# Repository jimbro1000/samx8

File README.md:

---
title: 'SAMx8: Dragon 64 512K SRAM board'
author:
- Ciaran Anscomb
...

Iterating on the SAMx4, the SAMx8 is a 512K RAM expansion and MMU for the
Dragon 64.  It enables arbitrary mapping of 16K pages in two tasks, optionally
making either of the highest two 4K areas common to all memory maps.

Because fast SRAM is used, and because the SAMx8 completely replaces the SAM,
video can be supported when the CPU is running at double rate.  The video base
address can be set to any multiple of 32 bytes across the entire 512K.

As this was partly an exercise in seeing what could be fit into the same sized
CPLD as the SAMx4, some features of the SAM are lost, e.g. Address-Dependent
CPU rate and the undocumented video address "glitching".

This design selects components available at the time of writing, but it should
be noted that some of these are end of life.  Hopefully, the VHDL code being
available will enable similar small and cheap designs with alternate
programmable logic chips.

**Warning:** Fitting this board requires a modification to the original
motherboard.  Although the Dragon 64 PCB is pretty robust, this is old
hardware, so I do not recommend trying this if you're not confident in your
desoldering skills: lifted pads or tracks may ensue.

Released under the Creative Commons Attribution-ShareAlike 4.0 International
License (CC BY-SA 4.0).  Full text in the LICENSE file.

## Files

`pcb/` contains KiCad schematic and PCB designs.

`cpld/` contains VHDL source for the Xilinx XC95144XL CPLD.  Either open the
`samx8.xise` project file in ISE or source the ISE environment files and run
`make` in this directory (GNU Make required).

`doc/` contains LaTeX and drawtiming source for the documentation.

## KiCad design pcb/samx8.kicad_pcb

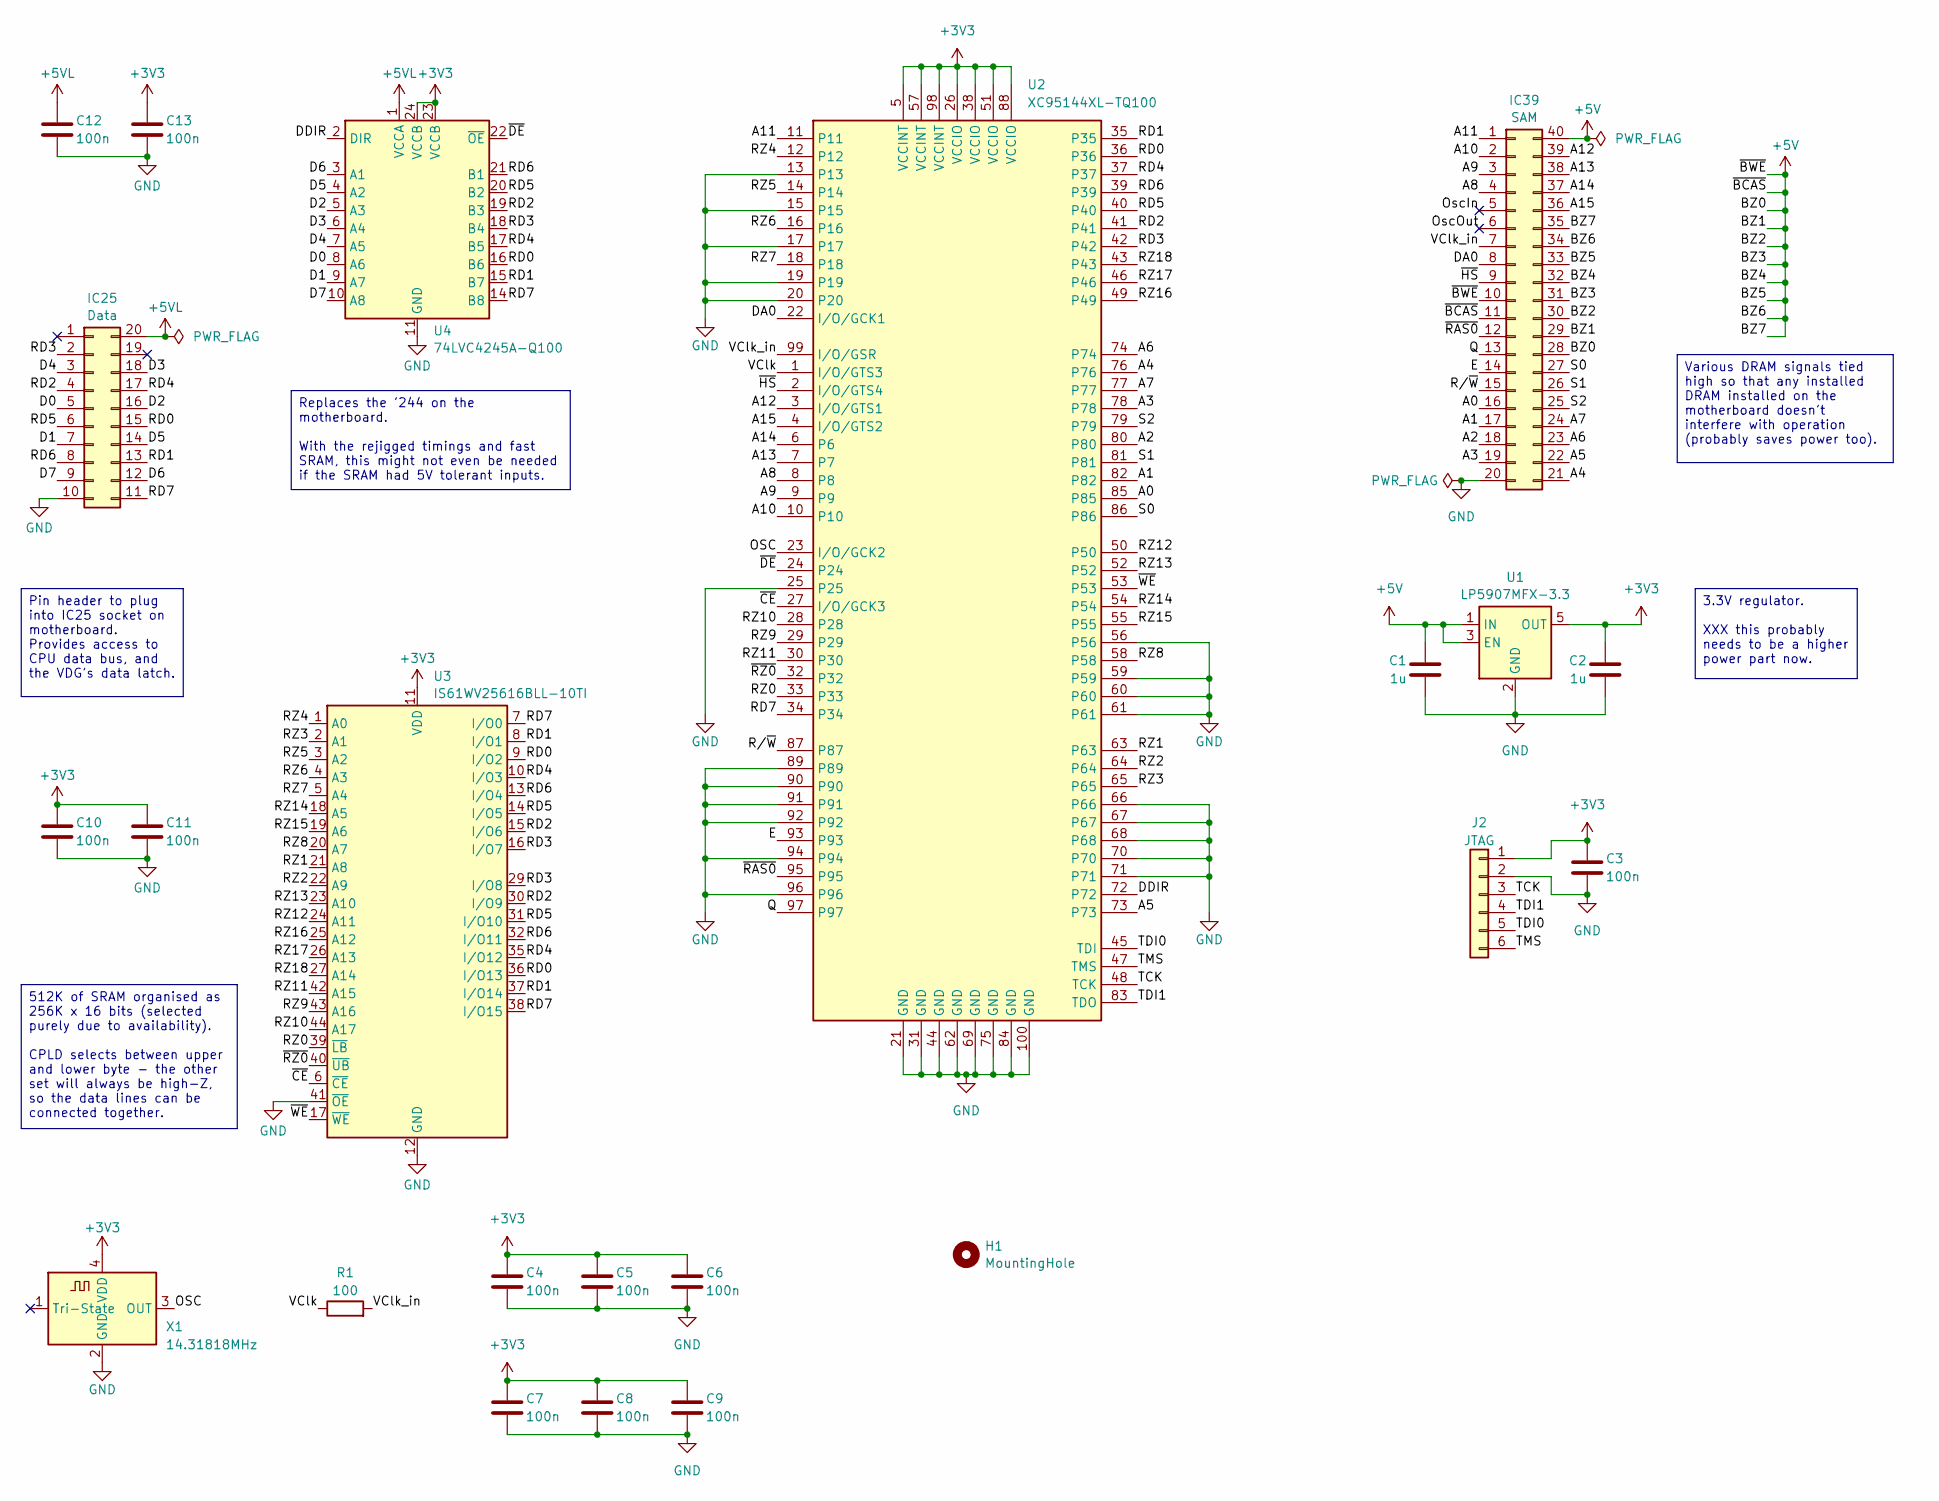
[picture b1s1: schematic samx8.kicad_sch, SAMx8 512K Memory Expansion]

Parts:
C1, C2: 1u; C_0805_2012Metric; LCSC Part C28323
C3, C4, C5, C6, C7, C8, C9, C10, C11, C12, C13: 100n; C_0402_1005Metric; JLCPCB BOM 0
H1: MountingHole; MountingHole_2.2mm_M2
IC25: Data; DIP-20_W7.62mm
IC39: SAM; DIP-40_W15.24mm; JLCPCB BOM 0
J2: JTAG; PinHeader_1x06_P2.54mm_Vertical; JLCPCB BOM 0
R1: 100; R_0603_1608Metric; LCSC Part C22775
U1: LP5907MFX-3.3; SOT-23-5; LCSC Part C80670
U2: XC95144XL-TQ100; TQFP-100_14x14mm_P0.5mm; LCSC Part C45126
U3: IS61WV25616BLL-10TI; TSOP-II-44_10.16x18.41mm_P0.8mm; LCSC Part C53825
U4: 74LVC4245A-Q100; TSSOP-24_4.4x7.8mm_P0.65mm; LCSC Part C548801
X1: 14.31818MHz; Oscillator_SMD_ECS_2520MV-xxx-xx-4Pin_2.5x2.0mm; LCSC Part C5119017

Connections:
+3V3: C2.1, C3.1, C4.1, C5.1, C6.1, C7.1, C8.1, C9.1, C10.1, C11.1, C13.1, J2.1, U1.5 (OUT), U2.5 (VCCINT), U2.26 (VCCIO), U2.38 (VCCIO), U2.51 (VCCIO), U2.57 (VCCINT), U2.88 (VCCIO), U2.98 (VCCINT), U3.11 (VDD), U3.33 (VDD), U4.23 (VCCB), U4.24 (VCCB), X1.4 (VDD)
+5V: C1.1, IC39.10, IC39.11, IC39.28, IC39.29, IC39.30, IC39.31, IC39.32, IC39.33, IC39.34, IC39.35, IC39.40, U1.1 (IN), U1.3 (EN)
+5VL: C12.1, IC25.20, U4.1 (VCCA)
/A0: IC39.16, U2.85
/A1: IC39.17, U2.82
/A2: IC39.18, U2.80
/A3: IC39.19, U2.78
/A4: IC39.21, U2.76
/A5: IC39.22, U2.73
/A6: IC39.23, U2.74
/A7: IC39.24, U2.77
/A8: IC39.4, U2.8
/A9: IC39.3, U2.9
/A10: IC39.2, U2.10
/A11: IC39.1, U2.11
/A12: IC39.39, U2.3 (I/O/GTS1)
/A13: IC39.38, U2.7
/A14: IC39.37, U2.6
/A15: IC39.36, U2.4 (I/O/GTS2)
/D0: IC25.5, U4.8 (A6)
/D1: IC25.7, U4.9 (A7)
/D2: IC25.16, U4.5 (A3)
/D3: IC25.18, U4.6 (A4)
/D4: IC25.3, U4.7 (A5)
/D5: IC25.14, U4.4 (A2)
/D6: IC25.12, U4.3 (A1)
/D7: IC25.9, U4.10 (A8)
/DA0: IC39.8, U2.22 (I/O/GCK1)
/DDIR: U2.72, U4.2 (DIR)
/E: IC39.14, U2.93
/OSC: U2.23 (I/O/GCK2), X1.3 (OUT)
/OscIn: IC39.5
/OscOut: IC39.6
/Q: IC39.13, U2.97
/RD0: IC25.15, U2.36, U3.9 (I/O2), U3.36 (I/O13), U4.16 (B6)
/RD1: IC25.13, U2.35, U3.8 (I/O1), U3.37 (I/O14), U4.15 (B7)
/RD2: IC25.4, U2.41, U3.15 (I/O6), U3.30 (I/O9), U4.19 (B3)
/RD3: IC25.2, U2.42, U3.16 (I/O7), U3.29 (I/O8), U4.18 (B4)
/RD4: IC25.17, U2.37, U3.10 (I/O3), U3.35 (I/O12), U4.17 (B5)
/RD5: IC25.6, U2.40, U3.14 (I/O5), U3.31 (I/O10), U4.20 (B2)
/RD6: IC25.8, U2.39, U3.13 (I/O4), U3.32 (I/O11), U4.21 (B1)
/RD7: IC25.11, U2.34, U3.7 (I/O0), U3.38 (I/O15), U4.14 (B8)
/RZ0: U2.33, U3.39 (~LB)
/RZ1: U2.63, U3.21 (A8)
/RZ2: U2.64, U3.22 (A9)
/RZ3: U2.65, U3.2 (A1)
/RZ4: U2.12, U3.1 (A0)
/RZ5: U2.14, U3.3 (A2)
/RZ6: U2.16, U3.4 (A3)
/RZ7: U2.18, U3.5 (A4)
/RZ8: U2.58, U3.20 (A7)
/RZ9: U2.29, U3.43 (A16)
/RZ10: U2.28, U3.44 (A17)
/RZ11: U2.30, U3.42 (A15)
/RZ12: U2.50, U3.24 (A11)
/RZ13: U2.52, U3.23 (A10)
/RZ14: U2.54, U3.18 (A5)
/RZ15: U2.55, U3.19 (A6)
/RZ16: U2.49, U3.25 (A12)
/RZ17: U2.46, U3.26 (A13)
/RZ18: U2.43, U3.27 (A14)
/R/~W: IC39.15, U2.87
/S0: IC39.27, U2.86
/S1: IC39.26, U2.81
/S2: IC39.25, U2.79
/TCK: J2.3, U2.48 (TCK)
/TDI0: J2.5, U2.45 (TDI)
/TDI1: J2.4, U2.83 (TDO)
/TMS: J2.6, U2.47 (TMS)
/VClk: R1.1, U2.1 (I/O/GTS3)
/VClk_in: IC39.7, R1.2, U2.99 (I/O/GSR)
/~CE: U2.27 (I/O/GCK3), U3.6 (~CE)
/~DE: U2.24, U4.22 (~OE)
/~HS: IC39.9, U2.2 (I/O/GTS4)
/~RAS0: IC39.12, U2.95
/~RZ0: U2.32, U3.40 (~UB)
/~WE: U2.53, U3.17 (~WE)
GND: C1.2, C2.2, C3.2, C4.2, C5.2, C6.2, C7.2, C8.2, C9.2, C10.2, C11.2, C12.2, C13.2, IC25.10, IC39.20, J2.2, U1.2 (GND), U2.13, U2.15, U2.17, U2.19, U2.20, U2.21 (GND), U2.25, U2.31 (GND), U2.44 (GND), U2.56, U2.59, U2.60, U2.61, U2.62 (GND), U2.66, U2.67, U2.68, U2.69 (GND), U2.70, U2.71, U2.75 (GND), U2.84 (GND), U2.89, U2.90, U2.91, U2.92, U2.94, U2.96, U2.100 (GND), U3.12 (GND), U3.34 (GND), U3.41 (~OE), U4.11 (GND), U4.12 (GND), U4.13 (GND), X1.2 (GND)

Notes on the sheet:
Pin header to plug into IC25 socket on motherboard. Provides access to CPU data bus, and the VDG's data latch.
Various DRAM signals tied high so that any installed DRAM installed on the motherboard doesn't interfere with operation (probably saves power too).
3.3V regulator. XXX this probably needs to be a higher power part now.
512K of SRAM organised as 256K x 16 bits (selected purely due to availability). CPLD selects between upper and lower byte - the other set will always be high-Z, so the data lines can be connected together.
Replaces the '244 on the motherboard. With the rejigged timings and fast SRAM, this might not even be needed if the SRAM had 5V tolerant inputs.

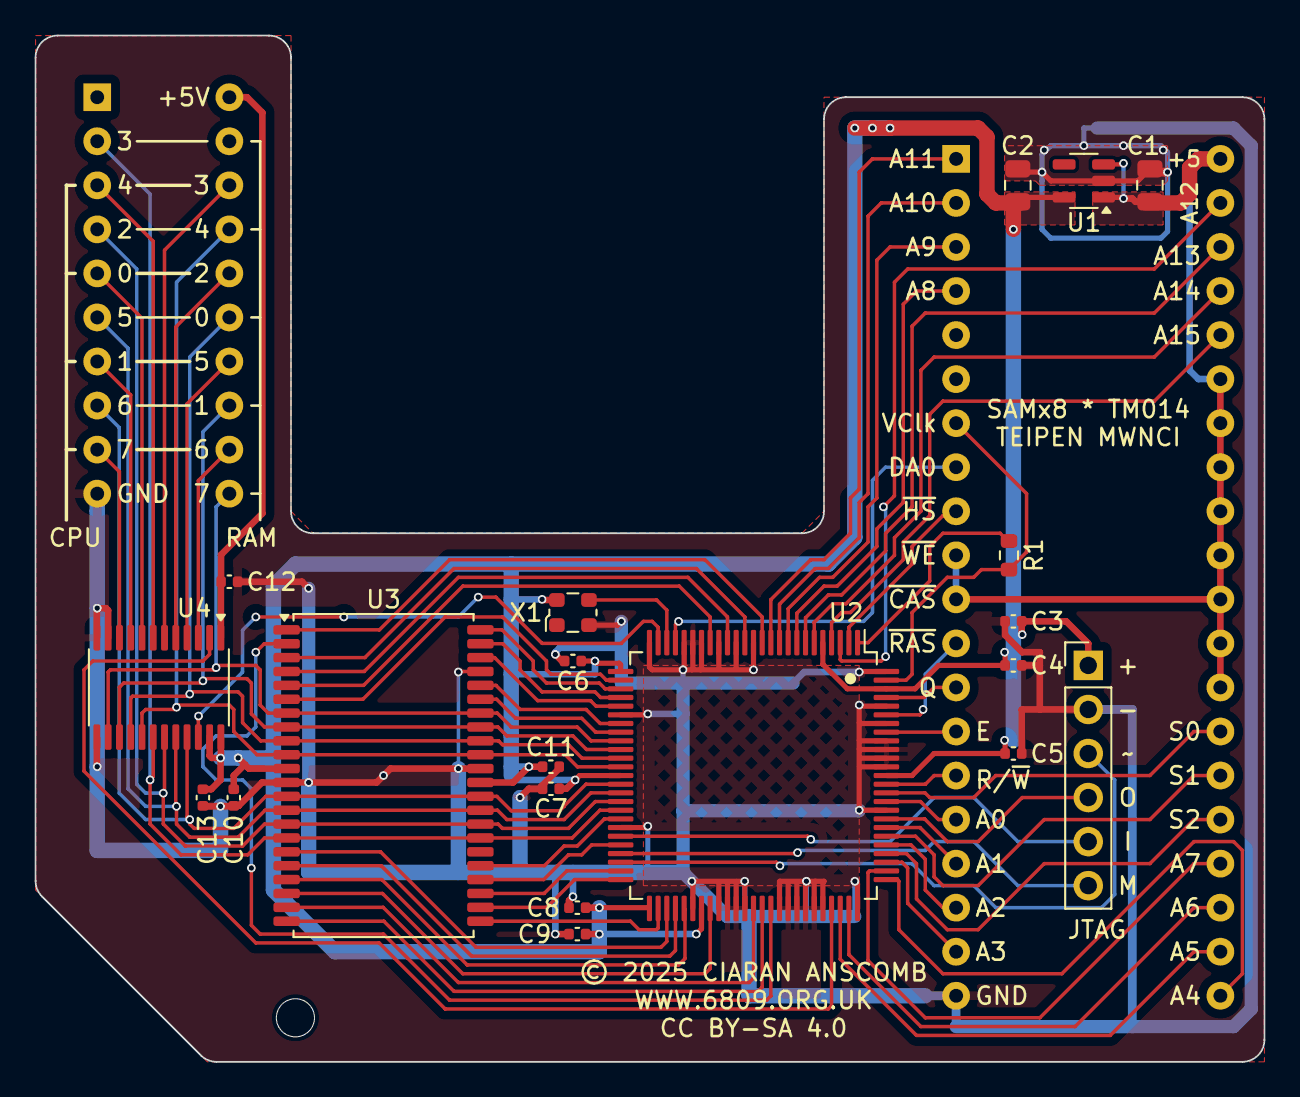
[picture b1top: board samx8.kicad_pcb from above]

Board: 2 copper layers, 70.9 x 59.2 mm, 23 parts (0 on the bottom side), 76 nets.

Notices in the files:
pcb/samx8.kicad_pcb:
© Ciaran Anscomb
© 2025 CIARAN ANSCOMB
CC BY-SA 4.0
